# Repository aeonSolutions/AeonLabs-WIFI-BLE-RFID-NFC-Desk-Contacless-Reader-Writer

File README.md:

# AeonLabs WIFI BLE RFID NFC Desk Contacless Reader Writer
 This repo contains the KiCad files for the  AeonLabs WIFI BLE RFID NFC Desk Contactless Reader Writer. This PCB adds WiFi and BLE capabilities to a OEM RFID NFC reader.
Features a RGB LED and a Buzzer and is designed to be mounted on existing commercial RFID NFC reader enclosures such as the one found [here](https://s.click.aliexpress.com/e/_9wRPxz) and [here](https://www.aliexpress.com/item/1005003803301443.html?spm=a2g0o.order_list.0.0.69ba1802ydCE38)

This PCB is best suited for home automation or commercial uses for #attendances #management at a factories or offices.

*Don't forget to LIKE , SHARE and subscribe the free whatsApp group* and if you liked this PCB consider buying me a cup of coffee. Links below.

### Status
  Running. Barcode & QRcode ; RFID waiting to be tested.

If you already tested this PCB send me a message. Thank you

## Revisions
- revision 3.1
  - Added Barcode & QR code wireless receiver for handheld scanners
  -  
- revision 2.3.1
  - Design and component placement corrections 

PCB fabrication of June 2022 (reviision 3.1) was sponsored by [PCBWay](www.pcbway.com)

## Liked it ? Get a Free PCB for yourself
Send me your Device or hardware and i will design a custom PCB for it. Free of charge. Contact-me on WhatsApp or email for more info. 

|  | *Don't forget to **LIKE** , **SHARE** and **subscribe** the free chat groups* and if you downloaded one of AeonLabs's PCBs consider sponsor  any open hardware project with a donation or a cup of coffee. Links on the top, right side pane and below. |
|-------------|------|

<br />
<br />

## Q&A WhatsApp/Telegram Groups
|  | Subscribe to the WhatsApp or Telegram channel to get latest information about any of this KiCad projects and get help. Or simply like this kind of projects and want to stay updated with the latest research ideas and prototypes during the day and week.   |
|-------------|------|

<br />
<br />
<br />

## Youtube Channel
|  | Subscribe to my Youtube channel for PCB assembly instruction or any other related to Artificial Intelligence, Smart devices and robotics. Link to the channel [here](https://www.youtube.com/channel/UCAewCBpMRPGCyFc1ET5CHJw). My most recent video is .... |
|-------------|------|

## Fully assembled PCB
Alternatively, and if you do not want to build a PCB by yourself and like to buy one, you can do it here:

The price will be around 30eur plus postage fees.
(I will also deliver the assembled PCB with all the components in place at a fair aditonal cost).

This PCB is a #direct fit #replacement of the one found on the internet at sale. For example here: https://s.click.aliexpress.com/e/_9wRPxz

#### Be supportive of my dedication and work towards technology education and buy me a coffee. Link below.

________________________________________________________________________________________________________________
## [Go back to main catalogue page](https://github.com/aeonSolutions/PCB-Prototyping-Catalogue)
________________________________________________________________________________________________________________

## PCB Parts list
- DC2DC converter HX4002B x2 : https://s.click.aliexpress.com/e/_Ak7IPx
- Capacitor 100nF SMD 1206 : https://s.click.aliexpress.com/e/_AVdmzr
- Capacitor 2.2uF SMD 1206 : https://s.click.aliexpress.com/e/_AVdmzr
- Resistor SMD 1206 330R x3 : https://s.click.aliexpress.com/e/_A7OXrR
- ESP32 WROOM32 x1 : https://s.click.aliexpress.com/e/_AF7N6l
- Buzzer x1: https://s.click.aliexpress.com/e/_AF7N6l
- LED RGB x1: https://s.click.aliexpress.com/e/_AccXHT
- RFID RC522 x1 (optional) : https://s.click.aliexpress.com/e/_Am0LAH

## Firmware Download 
one can use the PCB in the repository [AeonLabs-MCU-Burner-USB-to-UART-TTL](https://github.com/aeonSolutions/AeonLabs-MCU-Burner-USB-to-UART-TTL) to program the ESP32 WROOM32 MCU on this PCB.

______________________________________________________________________________________________________________________________

______________________________________________________________________________________________________________________________
### PCB Fabrication

<br />
<br />
<br />

______________________________________________________________________________________________________________________________
### License
2022 Creative Commons Attribution-NonCommercial-ShareAlike 4.0 International

https://creativecommons.org/licenses/by-nc-sa/4.0/

______________________________________________________________________________________________________________________________

<br />
<br />

### Be supportive of my dedication and work towards technology education and buy me a cup of coffee
Buy me a cup of coffee, a slice of pizza or a book to help me study, eat and think new PCB design files.

<br />
<br />

### Make a donation on Paypal
Make a donation on paypal and get a TAX refund*.

### Support all these open hardware projects and become a patreon  
Liked any of my PCB KiCad Designs? Help and Support my open work to all by becomming a LDAD Patreon.
In return I will give a free PCB design in KiCad to all patreon supporters. To learn more go to patreon.com. Link below.

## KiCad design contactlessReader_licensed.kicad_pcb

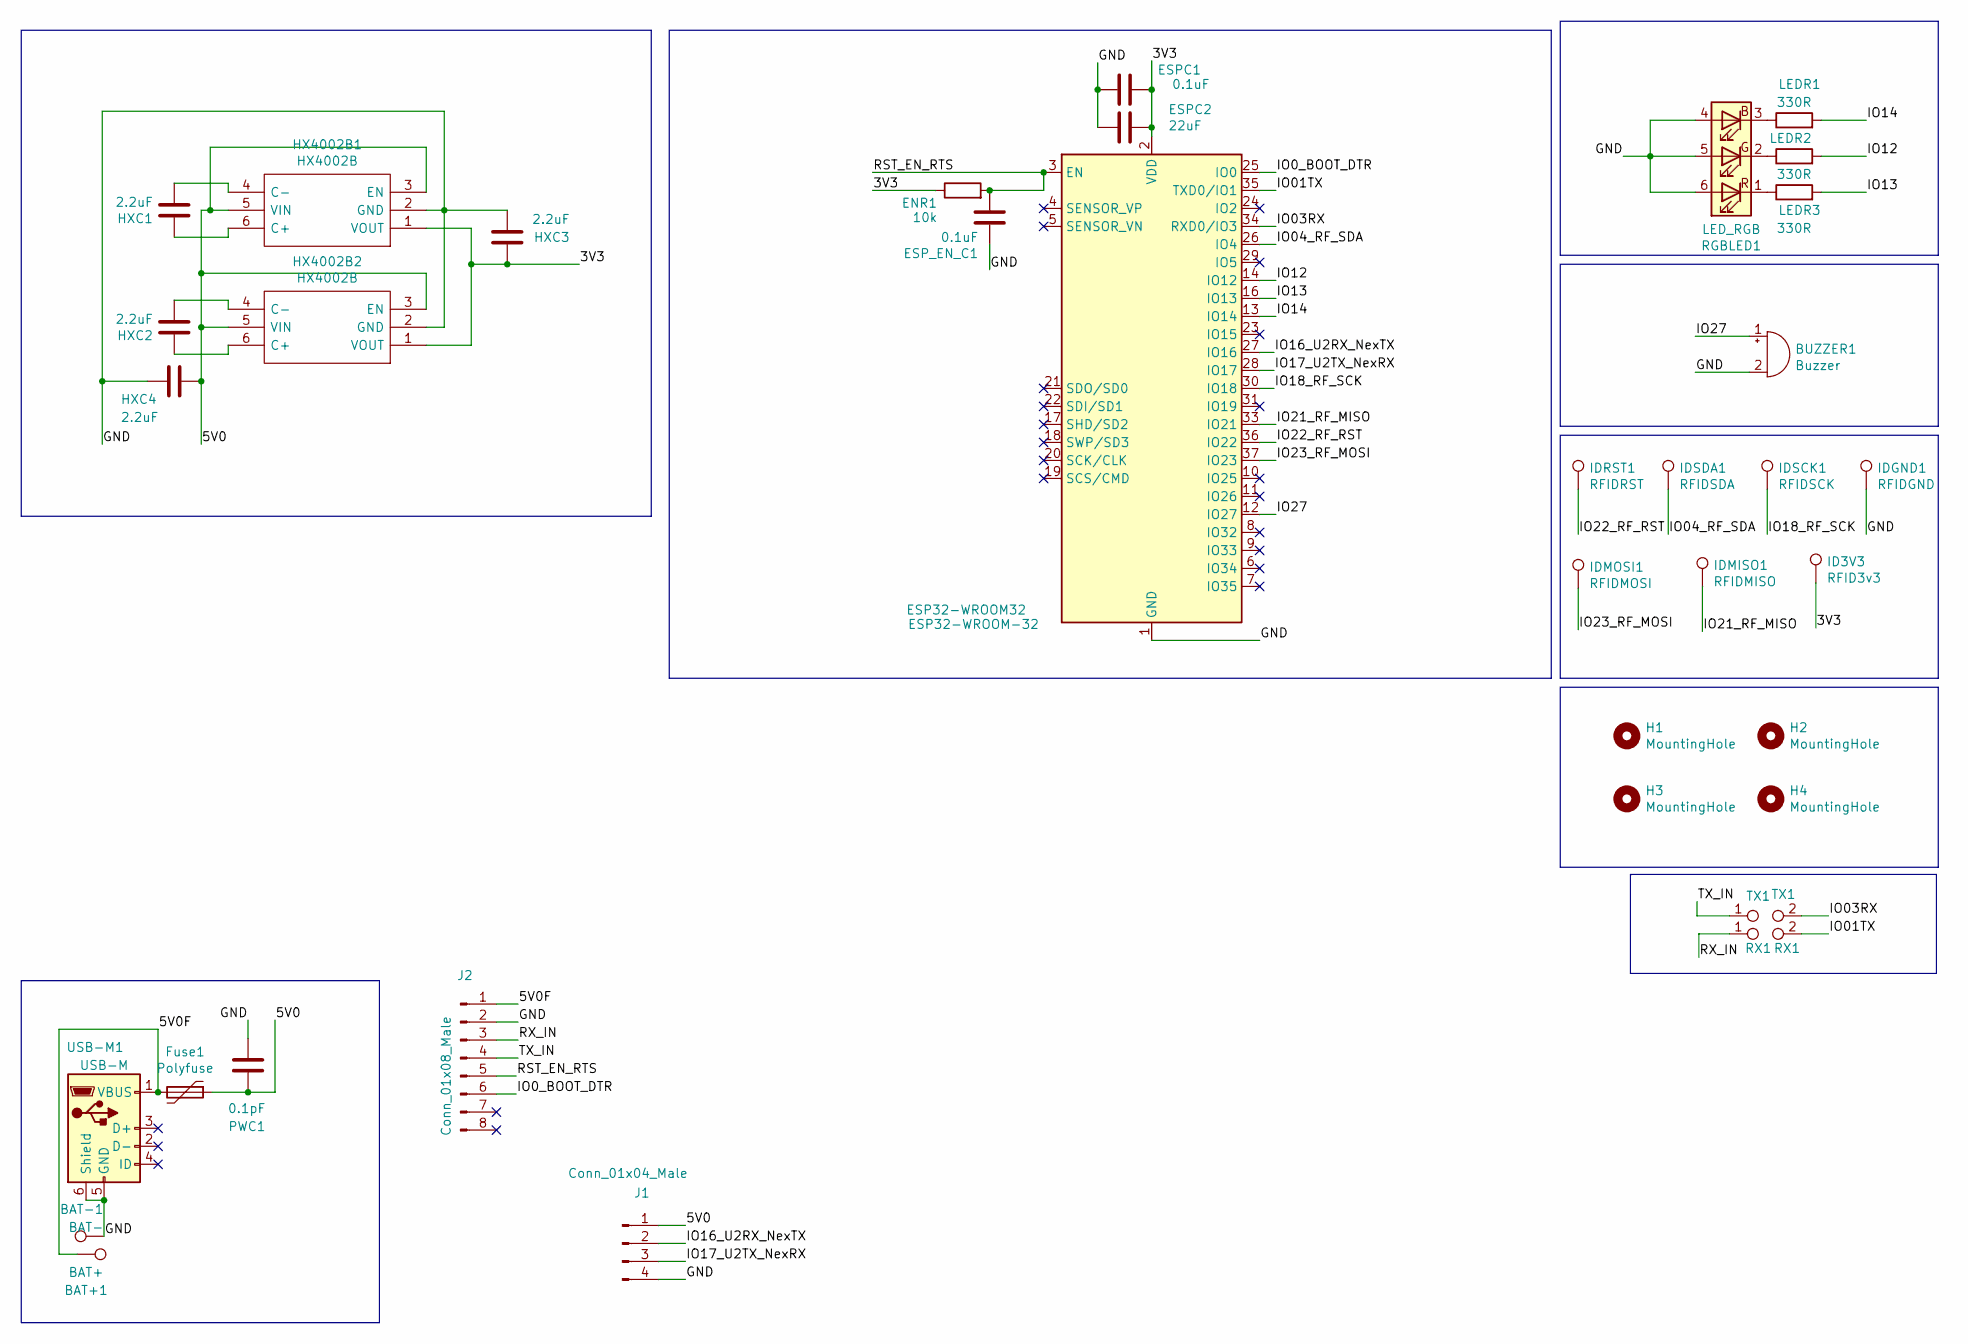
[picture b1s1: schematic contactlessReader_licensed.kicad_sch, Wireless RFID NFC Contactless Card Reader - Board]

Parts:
BAT+1: BAT+; TestPoint_THTPad_2.0x2.0mm_Drill1.0mm
BAT-1: BAT-; TestPoint_THTPad_2.0x2.0mm_Drill1.0mm
BUZZER1: Buzzer; MagneticBuzzer_Kobitone_254-EMB84Q-RO
ENR1: 10k; R_1206_3216Metric_Pad1.30x1.75mm_HandSolder
ESP32-WROOM32: ESP32-WROOM-32
ESPC1: 0.1uF; C_1206_3216Metric_Pad1.33x1.80mm_HandSolder
ESPC2: 22uF; C_1206_3216Metric_Pad1.33x1.80mm_HandSolder
ESP_EN_C1: 0.1uF; C_1206_3216Metric_Pad1.33x1.80mm_HandSolder
Fuse1: Polyfuse; Fuse_1206_3216Metric_Pad1.42x1.75mm_HandSolder
H1, H2, H3, H4: MountingHole; MountingHole_6.5mm
HX4002B1, HX4002B2: HX4002B; HX4002 SOT95 P280X125-6N; Manufacturer_Part_Number HX4002
HXC1, HXC2, HXC3, HXC4: 2.2uF; C_1206_3216Metric_Pad1.33x1.80mm_HandSolder
ID3V3: RFID3v3; TestPoint_THTPad_2.0x2.0mm_Drill1.0mm
IDGND1: RFIDGND; TestPoint_THTPad_2.0x2.0mm_Drill1.0mm
IDMISO1: RFIDMISO; TestPoint_THTPad_2.0x2.0mm_Drill1.0mm
IDMOSI1: RFIDMOSI; TestPoint_THTPad_2.0x2.0mm_Drill1.0mm
IDRST1: RFIDRST; TestPoint_THTPad_2.0x2.0mm_Drill1.0mm
IDSCK1: RFIDSCK; TestPoint_THTPad_2.0x2.0mm_Drill1.0mm
IDSDA1: RFIDSDA; TestPoint_THTPad_2.0x2.0mm_Drill1.0mm
J1: Conn_01x04_Male; JST_EH_B4B-EH-A_1x04_P2.50mm_Vertical
J2: Conn_01x08_Male; SOIC_clipProgSmall
LEDR1, LEDR2, LEDR3: 330R; R_1206_3216Metric_Pad1.30x1.75mm_HandSolder
PWC1: 0.1pF; C_1206_3216Metric_Pad1.33x1.80mm_HandSolder
RGBLED1: LED_RGB; LED_D5.0mm-4_RGB_Wide_Pins
RX1: RX1; TestPoint_Pad_Bridge_1.0x1.0mm
TX1: TX1; TestPoint_Pad_Bridge_1.0x1.0mm
USB-M1: USB-M; Micro_USB_pcb_socket_5pin_4weld_points

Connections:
/3V3: ENR1.1, ESP32-WROOM32.2 (VDD), ESPC1.1, ESPC2.1, HX4002B1.1 (VOUT), HX4002B2.1 (VOUT), HXC3.1, ID3V3.1
/5V0: Fuse1.1, HX4002B1.3 (EN), HX4002B1.5 (VIN), HX4002B2.3 (EN), HX4002B2.5 (VIN), HXC4.1, J1.1, PWC1.1
/5V0F: BAT+1.1, Fuse1.2, J2.1, USB-M1.1 (VBUS)
/GND: BAT-1.1, BUZZER1.2 (+), ESP32-WROOM32.1 (GND), ESP32-WROOM32.15 (GND), ESP32-WROOM32.38 (GND), ESP32-WROOM32.39 (GND), ESPC1.2, ESPC2.2, ESP_EN_C1.1, HX4002B1.2 (GND), HX4002B2.2 (GND), HXC3.2, HXC4.2, IDGND1.1, J1.4, J2.2, PWC1.2, RGBLED1.4 (BA), RGBLED1.5 (GA), RGBLED1.6 (RA), USB-M1.5 (GND), USB-M1.6 (Shield)
/IO0_BOOT_DTR: ESP32-WROOM32.25 (IO0), J2.6
/IO01TX: ESP32-WROOM32.35 (TXD0/IO1), RX1.2
/IO03RX: ESP32-WROOM32.34 (RXD0/IO3), TX1.2
/IO04_RF_SDA: ESP32-WROOM32.26 (IO4), IDSDA1.1
/IO12: ESP32-WROOM32.14 (IO12), LEDR2.2
/IO13: ESP32-WROOM32.16 (IO13), LEDR3.2
/IO14: ESP32-WROOM32.13 (IO14), LEDR1.2
/IO16_U2RX_NexTX: ESP32-WROOM32.27 (IO16), J1.2
/IO17_U2TX_NexRX: ESP32-WROOM32.28 (IO17), J1.3
/IO18_RF_SCK: ESP32-WROOM32.30 (IO18), IDSCK1.1
/IO21_RF_MISO: ESP32-WROOM32.33 (IO21), IDMISO1.1
/IO22_RF_RST: ESP32-WROOM32.36 (IO22), IDRST1.1
/IO23_RF_MOSI: ESP32-WROOM32.37 (IO23), IDMOSI1.1
/IO27: BUZZER1.1 (-), ESP32-WROOM32.12 (IO27)
/RST_EN_RTS: ENR1.2, ESP32-WROOM32.3 (EN), ESP_EN_C1.2, J2.5
/RX_IN: J2.3, RX1.1
/TX_IN: J2.4, TX1.1
unnamed: HX4002B1.4 (C-), HXC1.2
unnamed: HX4002B1.6 (C+), HXC1.1
unnamed: HX4002B2.4 (C-), HXC2.2
unnamed: HX4002B2.6 (C+), HXC2.1
unnamed: LEDR1.1, RGBLED1.3 (BK)
unnamed: LEDR2.1, RGBLED1.2 (GK)
unnamed: LEDR3.1, RGBLED1.1 (RK)

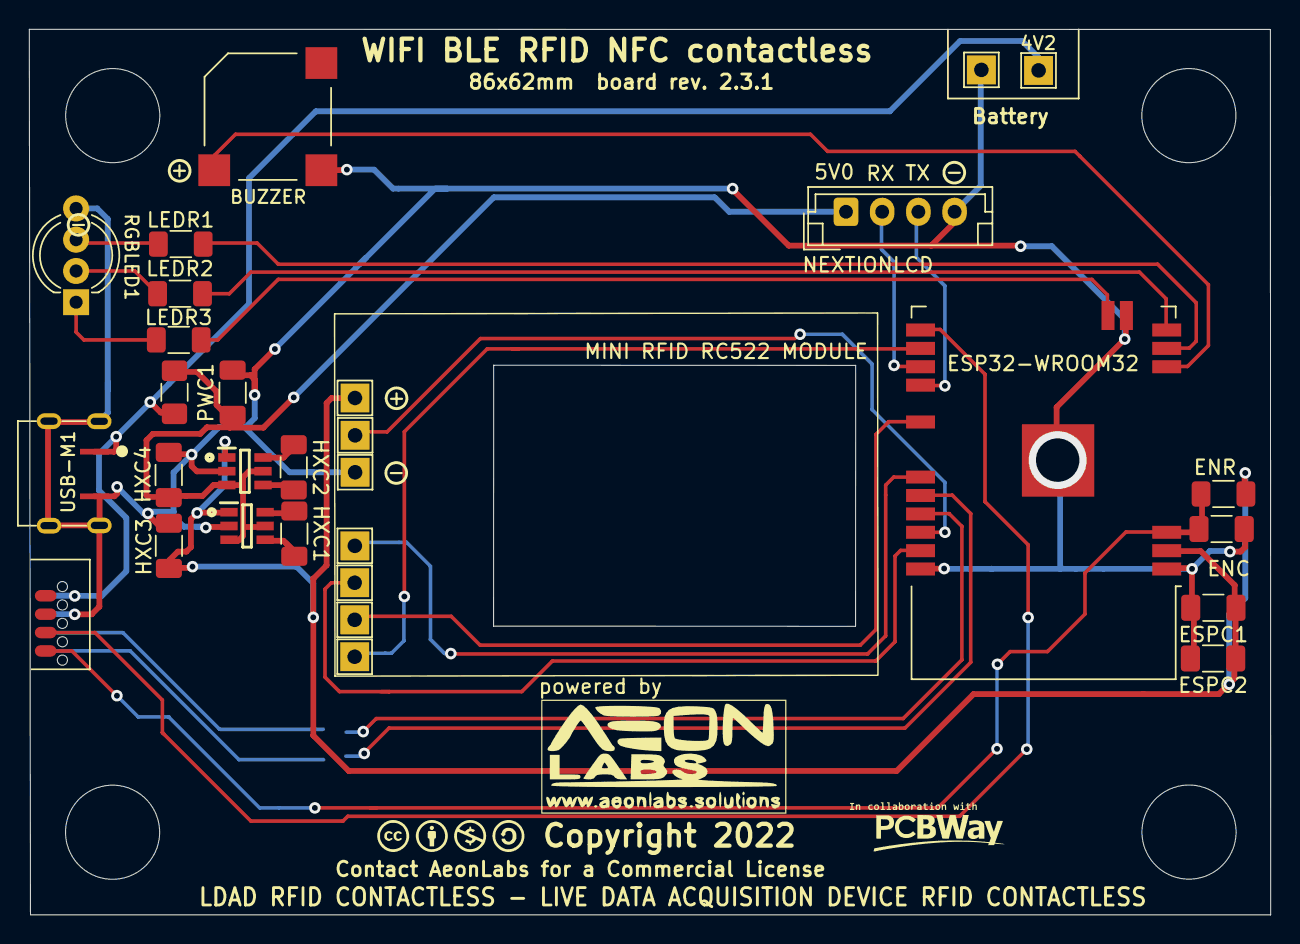
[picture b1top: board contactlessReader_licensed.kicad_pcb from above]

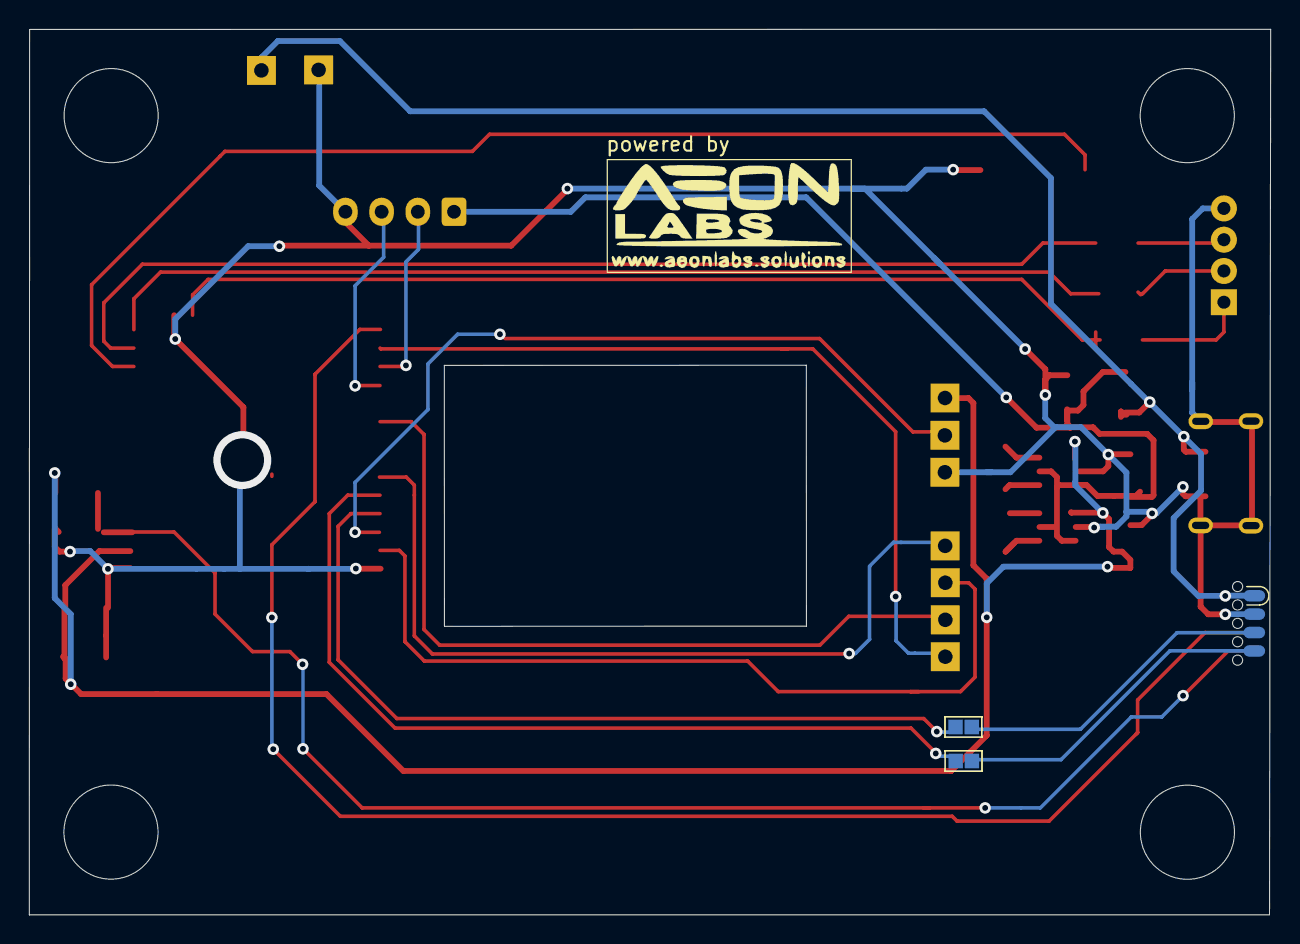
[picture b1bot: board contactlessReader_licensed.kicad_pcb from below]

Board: 2 copper layers, 85.7 x 61.2 mm, 36 parts (3 on the bottom side), 28 nets.

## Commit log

2022-04-01 init comm
2022-04-01 kicad files
2022-04-23 rev. 2.3.1

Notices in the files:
contactlessReader_licensed.kicad_pcb:
Copyright 2022
